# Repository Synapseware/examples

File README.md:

examples
========

## About
Includes lots of example projects and miscelaneous small projects that I didn't think warranted their own repository.  Mostly experiemental, actually largely experimental, these are just my working notes and areas to experiment.  There are some legit example projects though.

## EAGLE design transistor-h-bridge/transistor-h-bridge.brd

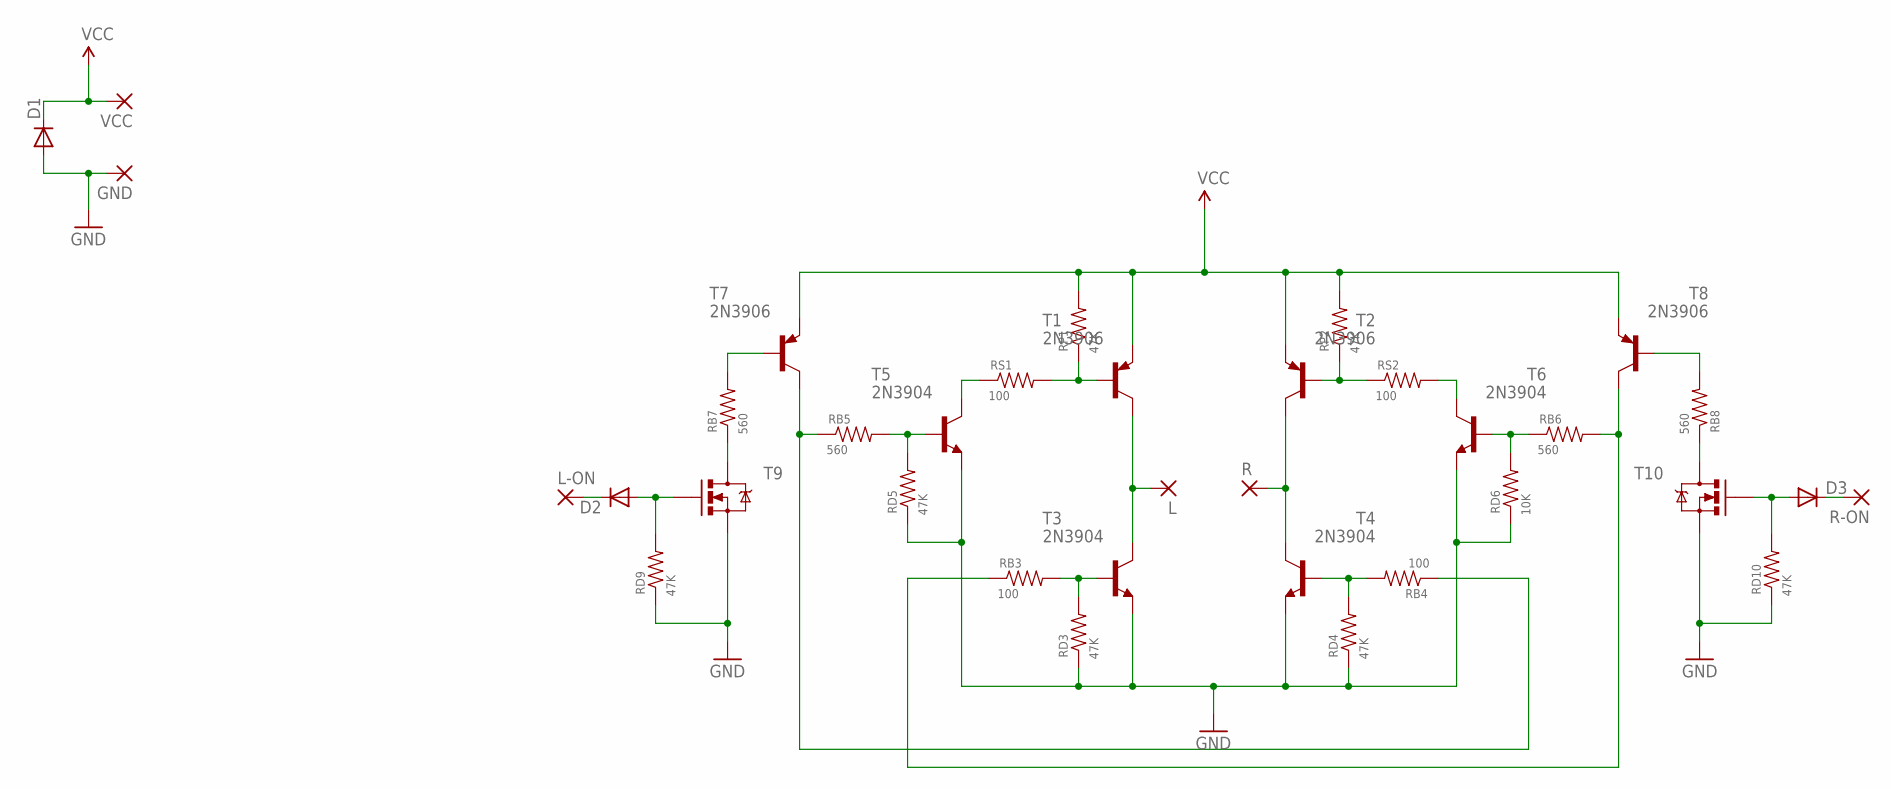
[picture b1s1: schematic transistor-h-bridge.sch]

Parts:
D1, D2, D3: DIODE1N4148; DIODE-1N4148
GND: WIREPAD2,54/0,8; 2,54/0,8
L: WIREPAD2,54/0,8; 2,54/0,8
L-ON: WIREPAD2,54/0,8; 2,54/0,8
R: WIREPAD2,54/0,8; 2,54/0,8
R-ON: WIREPAD2,54/0,8; 2,54/0,8
RB3, RB4: 100; VERT-PTH
RB5, RB6, RB7, RB8: 560; VERT-PTH
RD3, RD4, RD5, RD9, RD10: 47K; VERT-PTH
RD6: 10K; VERT-PTH
RP1, RP2: 47K; VERT-PTH
RS1, RS2: 100; VERT-PTH
T1, T2, T7, T8: 2N3906; TO92
T3, T4, T5, T6: 2N3904; TO92
T9, T10: MOSFET-NCHANNELPTH; TO-92
VCC: WIREPAD2,54/0,8; 2,54/0,8

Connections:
GND: D1.A, GND.1, RD3.1, RD4.1, RD5.1, RD6.1, RD9.1, RD10.1, T3.3 (E), T4.3 (E), T5.3 (E), T6.3 (E), T9.2 (S), T10.2 (S)
unnamed: RP1.1, RS1.2, T1.2 (B)
unnamed: RP2.1, RS2.1, T2.2 (B)
unnamed: RB6.1, RD6.2, T6.2 (B)
unnamed: D2.A, RD9.2, T9.3 (G)
unnamed: RB5.2, RD5.2, T5.2 (B)
unnamed: RB4.1, RB5.1, T7.1 (C)
unnamed: RB4.2, RD4.2, T4.2 (B)
unnamed: RB3.1, RB6.2, T8.1 (C)
unnamed: RB3.2, RD3.2, T3.2 (B)
unnamed: RB7.2, T7.2 (B)
unnamed: RB8.2, T8.2 (B)
unnamed: RB7.1, T9.1 (D)
unnamed: L.1, T1.1 (C), T3.1 (C)
unnamed: R.1, T2.1 (C), T4.1 (C)
unnamed: RS1.1, T5.1 (C)
unnamed: RS2.2, T6.1 (C)
unnamed: D3.A, RD10.2, T10.3 (G)
unnamed: RB8.1, T10.1 (D)
unnamed: D2.C, L-ON.1
unnamed: D3.C, R-ON.1
VCC: D1.C, RP1.2, RP2.2, T1.3 (E), T2.3 (E), T7.3 (E), T8.3 (E), VCC.1

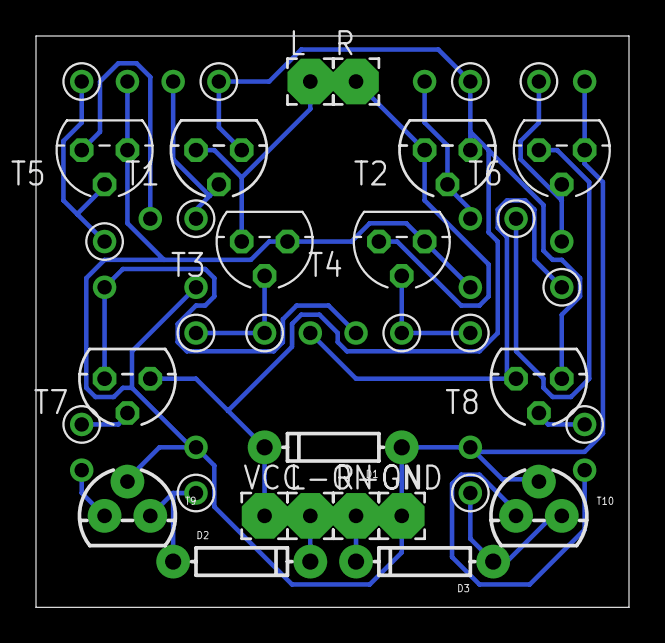
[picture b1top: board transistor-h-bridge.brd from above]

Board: 2 copper layers, 32.9 x 31.7 mm, 35 parts (0 on the bottom side), 22 nets.

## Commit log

2014-06-03 Adding sepic sample code (not functional)
2014-06-03 Adding more example projects
2014-06-03 Adding some template files
2014-06-07 Adding chip data examples
2014-08-04 Updating examples
2014-08-08 SMPS updates
2014-08-08 updates to example files
2014-10-31 Adding at25df321 driver example (no proven)
2014-10-31 example code nearly working - could be hardware problem, but data isn't being written/read successfully.
2014-10-31 Fixed hardware problem (had MISO and MOSI wired backwards) and added global protect/unprotect and sector protect/unprotect functions, as well as a BUSY status LED to indicate that the chip is busy fo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
2015-07-22 Files from old branch
2015-07-26 Adding atmega32u4 device info
2015-07-26 Adding interrupts for ATMega32u4
2015-07-26 Adding more info for interrupts
2015-07-26 Adding ADC and AC info
2015-07-26 Cleanup
2015-07-27 Updates to the SEPIC example.
2015-07-27 Updating readme
2015-07-27 Cleaning up project
2015-07-27 whitespace changes
2015-07-28 Adding arduino leonardo specs
2017-02-13 Updating chip docs
2017-02-23 Updating x68 example
    Adding ADC channel change function
2017-02-26 Misc updates
2017-03-20 New fuse defaults and updated examples
    New fuse defaults for a variety of ATMega and ATTiny parts.
    Updated chip data with additional helper functions to initialize certain
    hardware resources.
2017-08-18 attiny85 definitions
2017-08-29 Rename t85 file and add add'l settings
    Renamed the attiny85 example file, and added additional constants for
    the timer 0 and 1 prescalers.
2018-06-04 Updating t85 example code
2018-08-24 Adding example makefile (needs to be cleaned up)
2018-08-24 Make atpack makefile template generic
2018-08-24 Working on Tiny412 example
2018-08-25 Adding example project for ATTiny412
2018-08-25 Build / compile problem?
2018-08-25 Compiling initial program
2018-08-26 Updating makefile for new paths location
2018-08-26 Use pin3 and not pin7
2018-08-26 Updating part
    Programming is working after building avrdude 3.0 locally from sources.
2018-08-26 LED blink on timer ISR
2018-08-26 Adding README
2018-08-27 Rename attiny412 example folder
2019-09-19 New examples
2019-09-23 Tiny412 drivers
2019-09-24 Adding RTC driver
2019-12-05 Adding ESP32 example
2019-12-07 Adding example for ESP-01 module
2019-12-07 Temp logger working with ESP-01

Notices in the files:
parts and their libraries:
SparkFun-DiscreteSemi: Licensing: CC v3.0 Share-Alike You are welcome to use this library for commercial purposes.
